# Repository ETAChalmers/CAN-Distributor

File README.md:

CAN Distributor, to simplify connecting things to the CAN bus.

## RJ10 Pinout (4P4C)

Equivalent with RJ22.
Pinout is based on the CANOpen standard, as specified in:

https://www.phoenixcontact.com/assets/downloads_ed/global/web_dwl_technical_info/CANopen.pdf

## RJ45 Pinout (8P8C)

Pinout is based on the CANOpen standard, as specified in:

https://www.phoenixcontact.com/assets/downloads_ed/global/web_dwl_technical_info/CANopen.pdf

## Board Concept

Each distribution card delivers CAN and optionally power to its Nodes. Power is only distributed over the
Node ports. This is to avoid any complex problems regarding PSU load sharing, ground loops, etc...
Power is indicated by PWR_LED. Voltage and allowable current draw depends on the connected PSU.

It is not reasonable to draw more than 200/300 mA over the RJ10 cables.

The board has a footprint for a termination resistor, which may be populated. **The resistor should only be
populated if the board is at one of the two edges of the CAN network.**

The Main ports and Node ports use different connectors to avoid plugging them wrong. The RJ10 ports may 
either be populated with TE Connectivity's vertical [5520257-2](https://www.te.com/usa-en/product-5520257-2.html) connectors or horizontal [1-1705949-1](https://www.te.com/usa-en/product-1-1705949-1.html) connectors.

## Mechanical

All mounting holes are for M3.

The board can be mounted to a DIN rail using Phoenix Contact's [1201578](https://www.phoenixcontact.com/online/portal/se?uri=pxc-oc-itemdetail:pid=1201578&library=sesv&tab=1&selectedCategory=ALL) or [1200993](https://www.phoenixcontact.com/online/portal/se?uri=pxc-oc-itemdetail:pid=1200993&library=sesv&tab=1&selectedCategory=ALL) rail adapters.
In that case the board is screwed to the adapters using self tapping M3 plastic screws.

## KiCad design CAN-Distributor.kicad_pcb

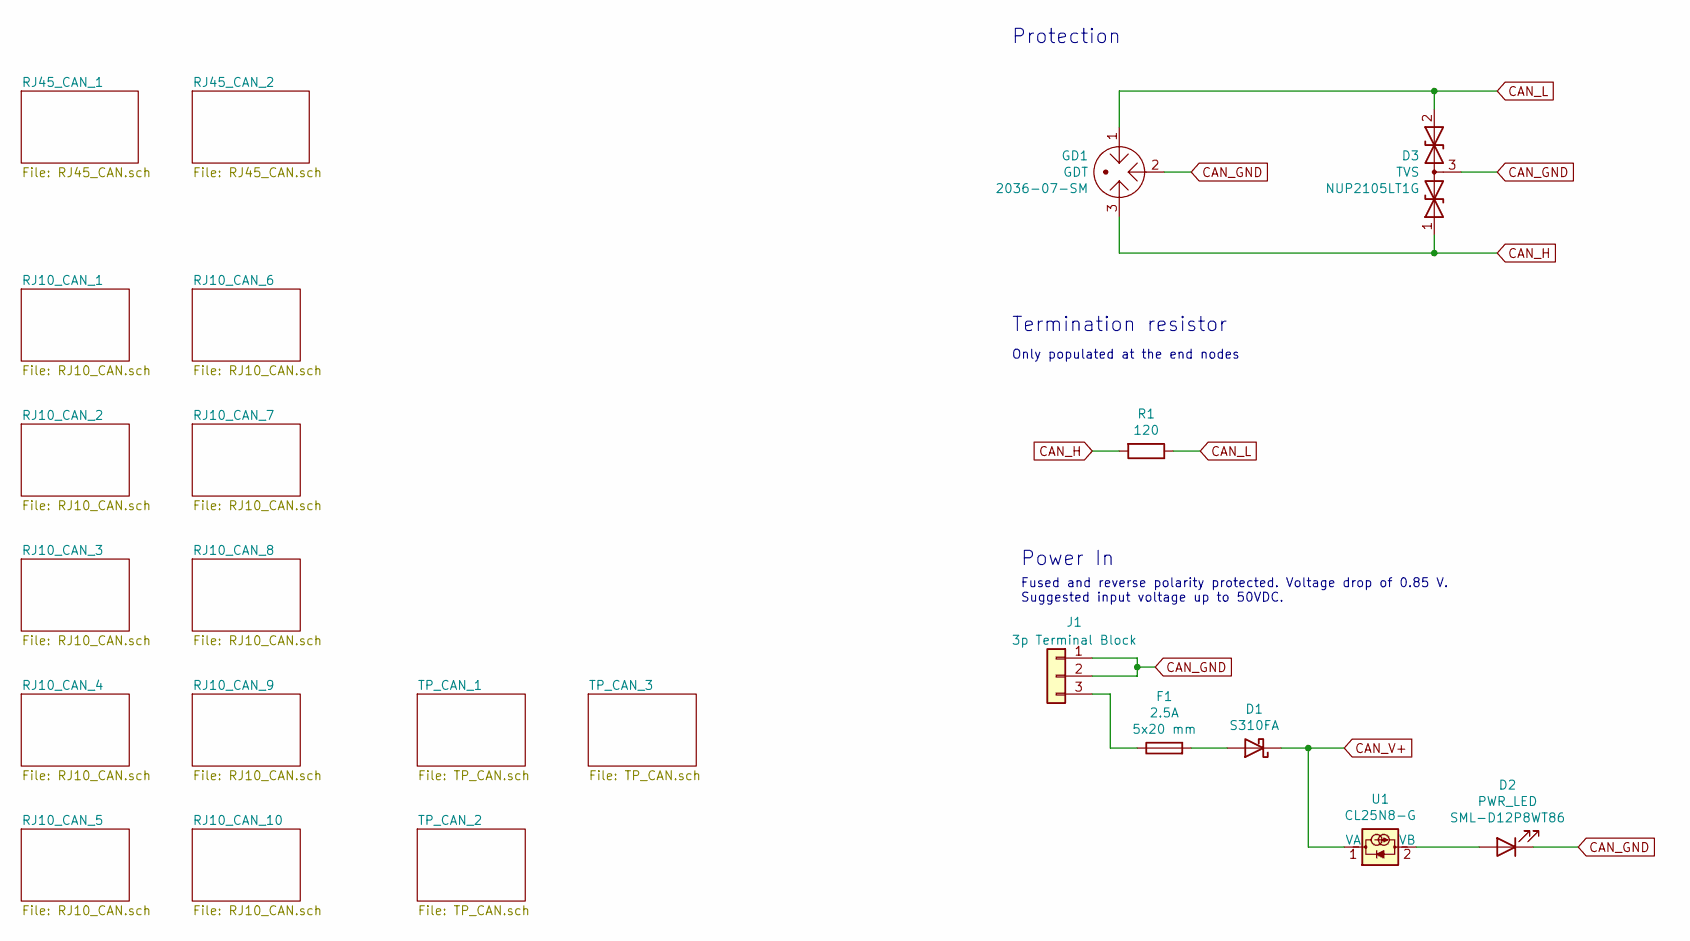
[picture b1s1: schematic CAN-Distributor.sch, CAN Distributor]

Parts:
D1: D_Schottky; D_SOD-123F; MPN S310FA; Farnell 2822559
D2: PWR_LED; D_0603_1608Metric; MPN SML-D12P8WT86; Farnell 2687486
D3: TVS; SOT-23; MPN NUP2105LT1G; Farnell 2101833
F1: 2.5A; Fuseholder_Cylinder-5x20mm_Schurter_0031_8201_Horizontal_Op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; MPN 0031.8201; Farnell 1162740
GD1: GDT; Bourns_Inc.-2036-07-SM-RPLF-MFG; MPN 2036-07-SM; Farnell 1846857
J1: 3p Terminal Block; TerminalBlock_bornier-3_P5.08mm
R1: 120; R_Axial_DIN0411_L9.9mm_D3.6mm_P15.24mm_Horizontal
U1: CL25N8-G; SOT-89-3; MPN CL25N8-G; Farnell 2448489

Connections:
CAN_GND: D2.1 (K), D3.3 (common), GD1.2, J1.1, J1.2; also elsewhere on the board
CAN_H: D3.1 (A1), GD1.3, R1.2; also elsewhere on the board
CAN_L: D3.2 (A2), GD1.1, R1.1; also elsewhere on the board
CAN_V+: D1.1 (K), U1.1 (VA); also elsewhere on the board
unnamed: D1.2 (A), F1.2
unnamed: D2.2 (A), U1.2 (VB)
unnamed: F1.1, J1.3

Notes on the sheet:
Only populated at the end nodes
Power In
Termination resistor
Fused and reverse polarity protected. Voltage drop of 0.85 V. Suggested input voltage up to 50VDC.
Protection

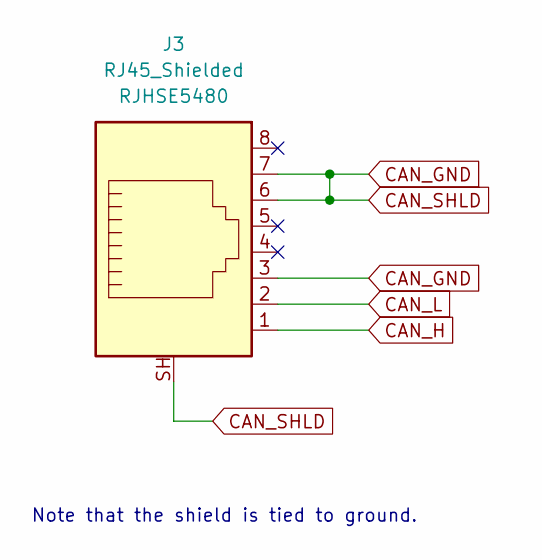
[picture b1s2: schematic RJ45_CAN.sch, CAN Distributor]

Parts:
J2: RJ45_Shielded; RJHSE5480; MPN RJHSE5480; Farnell 3367703

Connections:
CAN_GND: J2.3, J2.6, J2.7, J2.SH; also elsewhere on the board
CAN_H: J2.1; also elsewhere on the board
CAN_L: J2.2; also elsewhere on the board

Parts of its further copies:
J3: RJ45_Shielded; RJHSE5480; MPN RJHSE5480; Farnell 3367703

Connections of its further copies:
CAN_GND: J3.3, J3.6, J3.7, J3.SH; also elsewhere on the board
CAN_H: J3.1; also elsewhere on the board
CAN_L: J3.2; also elsewhere on the board

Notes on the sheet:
Note that the shield is tied to ground.

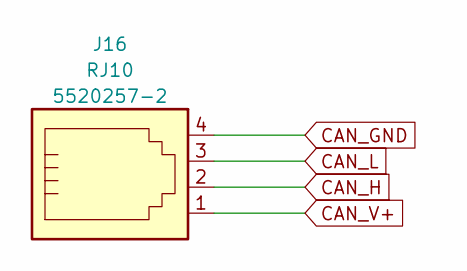
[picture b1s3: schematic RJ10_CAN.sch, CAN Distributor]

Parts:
J4: RJ10; TE_5520257-2; MPN 5520257-2; Farnell 1284339

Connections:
CAN_GND: J4.4; also elsewhere on the board
CAN_H: J4.2; also elsewhere on the board
CAN_L: J4.3; also elsewhere on the board
CAN_V+: J4.1; also elsewhere on the board

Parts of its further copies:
J5, J6, J7, J8, J9, J10, J11, J12, J16: RJ10; TE_5520257-2; MPN 5520257-2; Farnell 1284339

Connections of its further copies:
CAN_GND: J5.4, J6.4, J7.4, J8.4, J9.4, J10.4, J11.4, J12.4, J16.4; also elsewhere on the board
CAN_H: J5.2, J6.2, J7.2, J8.2, J9.2, J10.2, J11.2, J12.2, J16.2; also elsewhere on the board
CAN_L: J5.3, J6.3, J7.3, J8.3, J9.3, J10.3, J11.3, J12.3, J16.3; also elsewhere on the board
CAN_V+: J5.1, J6.1, J7.1, J8.1, J9.1, J10.1, J11.1, J12.1, J16.1; also elsewhere on the board

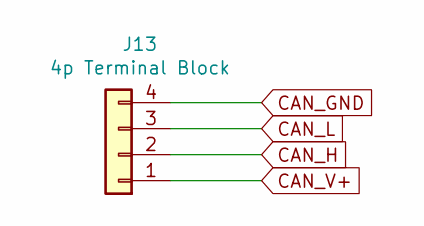
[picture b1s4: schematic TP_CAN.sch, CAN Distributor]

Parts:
J13: 4p Terminal Block; TerminalBlock_TE_282834-4_1x04_P2.54mm_Horizontal

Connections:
CAN_GND: J13.4; also elsewhere on the board
CAN_H: J13.2; also elsewhere on the board
CAN_L: J13.3; also elsewhere on the board
CAN_V+: J13.1; also elsewhere on the board

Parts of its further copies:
J14, J15: 4p Terminal Block; TerminalBlock_TE_282834-4_1x04_P2.54mm_Horizontal

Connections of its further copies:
CAN_GND: J14.4, J15.4; also elsewhere on the board
CAN_H: J14.2, J15.2; also elsewhere on the board
CAN_L: J14.3, J15.3; also elsewhere on the board
CAN_V+: J14.1, J15.1; also elsewhere on the board

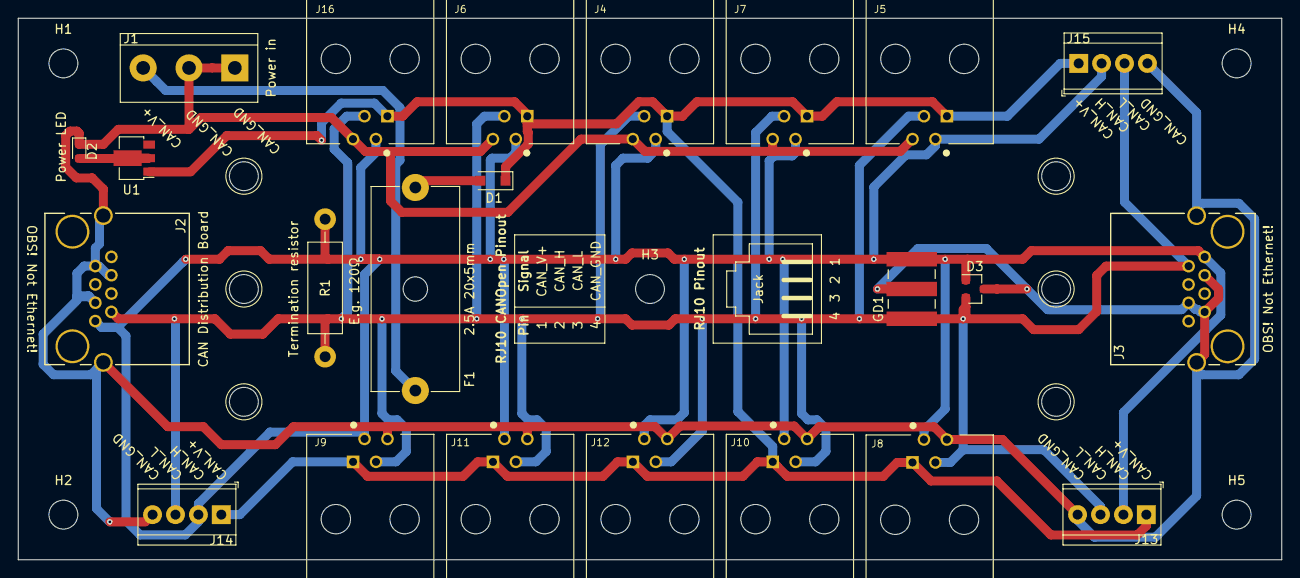
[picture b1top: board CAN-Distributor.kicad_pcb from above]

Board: 2 copper layers, 140.0 x 60.0 mm, 32 parts (0 on the bottom side), 7 nets.

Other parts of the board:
G1: RJ10_CAN_Open_Pinout_Table_Silkscreen
G2: RJ10_Pinout_Silkscreen
H1, H2, H3, H4, H5: MountingHole_3.2mm_M3_DIN965
M1, M2: DINRailAdapter_3xM3_PhoenixContact_1201578

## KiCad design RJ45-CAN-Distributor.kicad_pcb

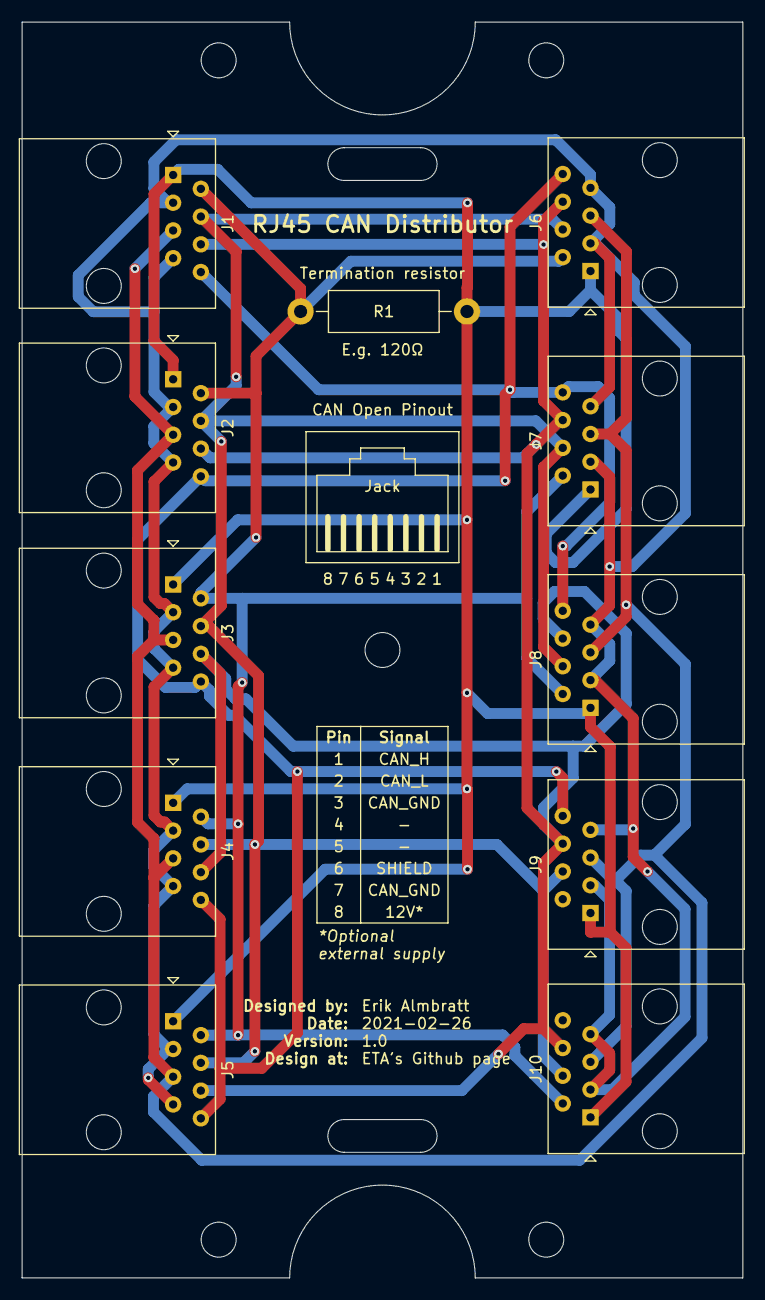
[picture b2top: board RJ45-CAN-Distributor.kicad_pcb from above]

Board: 2 copper layers, 66.0 x 115.0 mm, 17 parts (0 on the bottom side), 7 nets.

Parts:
G1: CAN_Open_Pinout_Table_Silkscreen
G2: CAN_Open_Pinout_Silkscreen
H1, H2, H3, H4: MountingHole_3.2mm_M3
J1, J2, J3, J4, J5, J6, J7, J8, J9, J10: RJ45; RJ45_Amphenol_54602-x08_Horizontal
R1: 120; R_Axial_DIN0411_L9.9mm_D3.6mm_P15.24mm_Horizontal

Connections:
CAN_GND: J1.3, J1.7, J2.3, J2.7, J3.3, J3.7, J4.3, J4.7, J5.3, J5.7, J6.3, J6.7, J7.3, J7.7, J8.3, J8.7, J9.3, J9.7, J10.3, J10.7
CAN_H: J1.1, J2.1, J3.1, J4.1, J5.1, J6.1, J7.1, J8.1, J9.1, J10.1, R1.2
CAN_L: J1.2, J2.2, J3.2, J4.2, J5.2, J6.2, J7.2, J8.2, J9.2, J10.2, R1.1
CAN_V+: J1.8, J2.8, J3.8, J4.8, J5.8, J6.8, J7.8, J8.8, J9.8, J10.8
Reserved1: J1.4, J2.4, J3.4, J4.4, J5.4, J6.4, J7.4, J8.4, J9.4, J10.4
Reserved2: J1.5, J2.5, J3.5, J4.5, J5.5, J6.5, J7.5, J8.5, J9.5, J10.5
SHIELD: J1.6, J2.6, J3.6, J4.6, J5.6, J6.6, J7.6, J8.6, J9.6, J10.6

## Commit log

2021-02-26 Create project. General design done.
2021-02-26 Route, associate and generate bom and drawings.
2021-02-26 Remove unnecessary xml file.
2021-04-02 Add RJ40 silksreens footprints and rename old RJ45 footprints.
2021-04-02 Change from RJ40 to RJ10. Typo....
2021-04-03 Remove RJ45 from project title.
2021-04-03 Design v2 circuit and make footprints.
2021-04-03 Perform layout. Add CAN testpoints.
2021-04-03 Autoroute board.
2021-04-03 Export documentation.
2021-04-03 Add a tenth RJ10 connector.
2021-04-03 Export documentation
2021-04-03 Upload images for documentation.
2021-04-04 Add protection TVS and GDT. Rename TP file.
2021-04-04 Update BOM with TVS and GDT.
2021-04-04 Add additional GND input
2021-05-20 Rotate RJ45 connectors and re-route.
